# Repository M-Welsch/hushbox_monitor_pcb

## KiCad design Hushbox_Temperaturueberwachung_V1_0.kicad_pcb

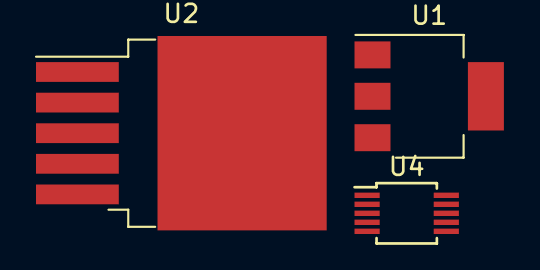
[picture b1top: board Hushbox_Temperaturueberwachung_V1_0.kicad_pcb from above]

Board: 2 copper layers, 3 parts (0 on the bottom side), 4 nets, no tracks yet.

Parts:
U1: AMS1117-5.0; SOT-223-3_TabPin2
U2: LM2596S-ADJ; TO-263-5_TabPin3
U4: AD5272BRMZ-20; MSOP-10_3x3mm_P0.5mm

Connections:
+5V: U1.2, U4.1, U4.7
+12V: U1.3, U2.1
/fb: U2.4, U4.2
GND: U1.1, U2.3, U2.5, U4.4, U4.6, U4.10

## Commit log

2022-04-02 first version that was acutally built up
